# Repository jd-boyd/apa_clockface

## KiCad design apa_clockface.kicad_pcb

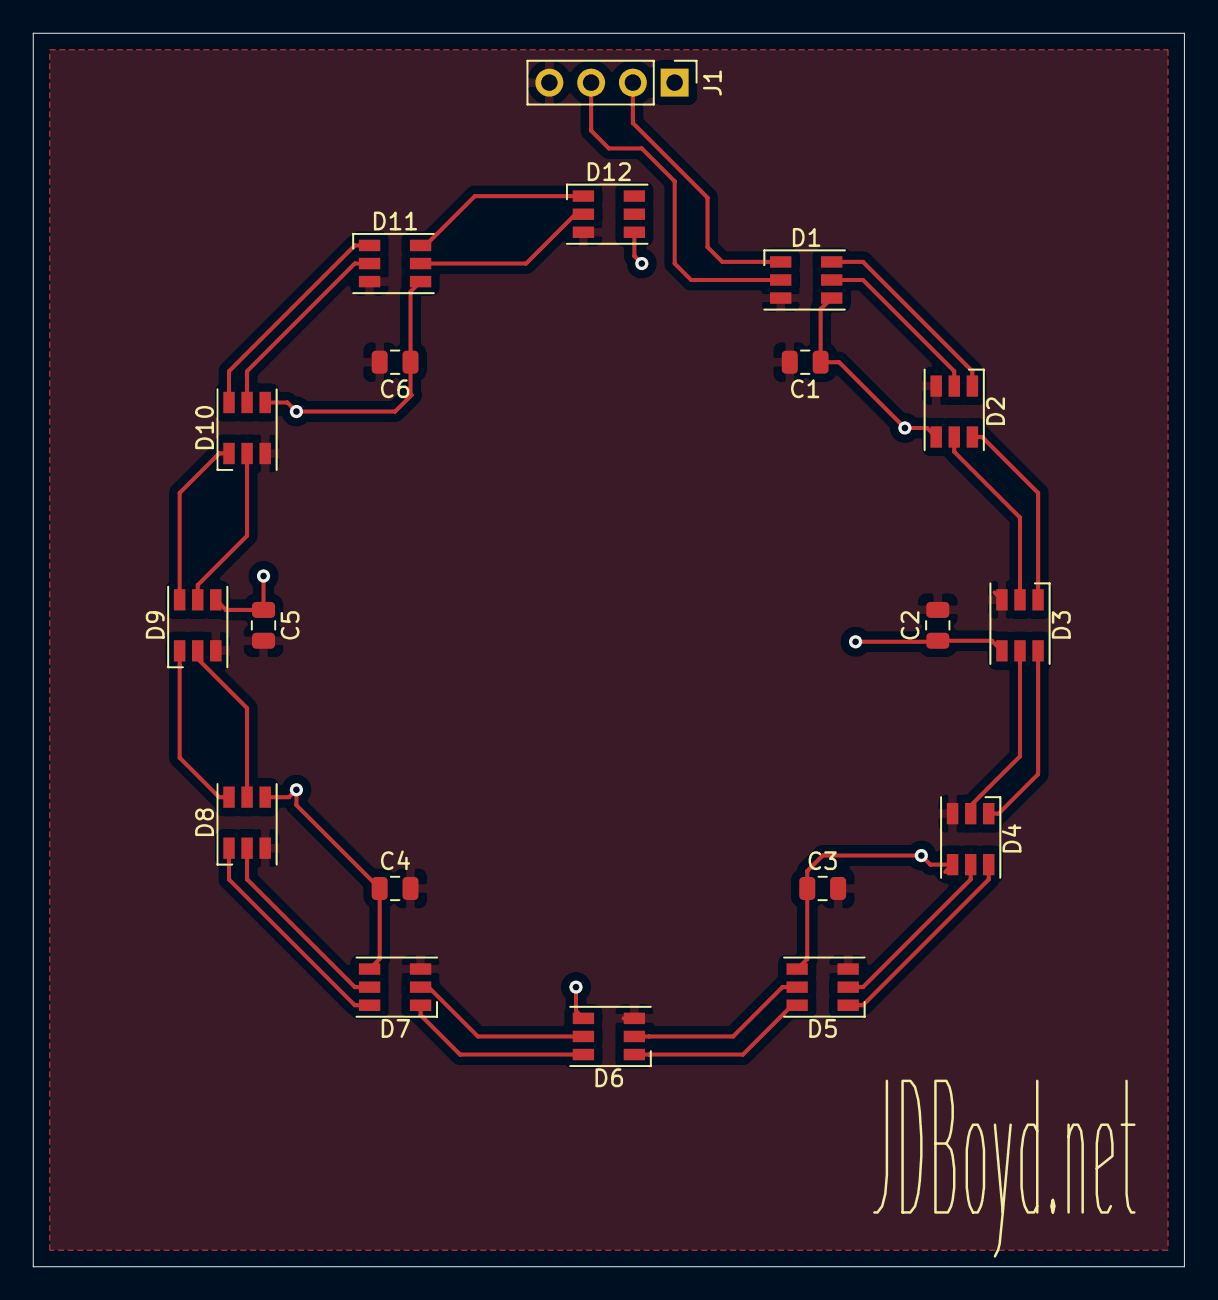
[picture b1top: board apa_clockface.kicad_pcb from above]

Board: 2 copper layers, 70.0 x 75.0 mm, 19 parts (0 on the bottom side), 26 nets.

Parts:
C1, C2, C3, C4, C5, C6: 0.1uF; C_0805_2012Metric
D1, D2, D3, D4, D5, D6, D7, D8, D9, D10, D11, D12: APA102; LED_RGB_PLCC-6
J1: Conn_01x04_Female; PinHeader_1x04_P2.54mm_Vertical

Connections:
+5V: C1.1, C2.1, C3.1, C4.1, C5.1, C6.1, D1.4, D2.4, D3.4, D4.4, D5.4, D6.4, D7.4, D8.4, D9.4, D10.4, D11.4, D12.4, J1.1
GND: C1.2, C2.2, C3.2, C4.2, C5.2, C6.2, D1.3, D2.3, D3.3, D4.3, D5.3, D6.3, D7.3, D8.3, D9.3, D10.3, D11.3, D12.3, J1.4
unnamed: D1.1, J1.2
unnamed: D1.2, J1.3
unnamed: D1.5, D2.2
unnamed: D1.6, D2.1
unnamed: D2.5, D3.2
unnamed: D2.6, D3.1
unnamed: D3.5, D4.2
unnamed: D3.6, D4.1
unnamed: D4.5, D5.2
unnamed: D4.6, D5.1
unnamed: D5.5, D6.2
unnamed: D5.6, D6.1
unnamed: D6.5, D7.2
unnamed: D6.6, D7.1
unnamed: D7.5, D8.2
unnamed: D7.6, D8.1
unnamed: D8.5, D9.2
unnamed: D8.6, D9.1
unnamed: D9.6, D10.1
unnamed: D9.5, D10.2
unnamed: D10.5, D11.2
unnamed: D10.6, D11.1
unnamed: D11.5, D12.2
unnamed: D11.6, D12.1

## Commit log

2019-06-24 Import work in progress.
    Schematic seems done.
    Layout still needs VCC routing to be finished.
    Also, I'm not happy with having the APAs rotated only be 90s, would prefer to
    also have 60s and 30s, along with curved traces, but at the moment I'm
    leaning towards getting it done instead of fighting with KiCad over choices
    here that I don't anticipate using again in other near term projects.
2019-07-05 Finish routing, change 1x4 connector.
